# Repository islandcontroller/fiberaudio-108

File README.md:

# fiberaudio-108

A low-cost USB audio interface with S/PDIF optical output, based on the Cmedia CM108AH ASIC.

<p align="center"><picture>
  <source media="(prefers-color-scheme: dark)" srcset="doc/block-schem-wh.svg" />
  <source media="(prefers-color-scheme: light)" srcset="doc/block-schem.svg" />
  
</picture></p>

View [**Schematic**](doc/sch_fiberaudio-108_rev5.pdf) :page_facing_up: or [**PCB Preview**](https://htmlpreview.github.io/?https://github.com/islandcontroller/fiberaudio-108/blob/master/doc/ibom.html) :globe_with_meridians:. Customize using the [**CM108AH Configuration Tool**](sw/README.md) :cd:.

Production files will be made available on the [Releases](https://github.com/islandcontroller/fiberaudio-108/releases) page, once validation is complete.

### Key features

* Cmedia CM108AH audio interface ASIC
* 2.0 Stereo, up to 16-bit/48kHz (CD-DA equivalent)
* USB Mini-B input
* Optical S/PDIF output (JIS F05, e.g. TOSLINK&trade;)
* USB Audio Device Class 1.0, uses generic drivers
* Configuration EEPROM

## Overview

This USB audio interface provides a low-cost S/PDIF optical output for portable computers and tablet devices. Audio tranmission via optical link - as opposed to a wired line-level connection - eliminates hum caused by ground potential differences, and noise feed-through from switched-mode power supplies.

| Design Requirement | Solution Approach |
|--------------------|-------------------|
| Provide electrical isolation between device and audio equipment | Audio signal transmission via optical link (e.g. TOSLINK&trade;) |
| Compatibility for wide range of operating systems, with minimal driver maintenance | USB Audio Device Class using OS-provided generic drivers |
| IP accessibility for PCB design files | Use of free, open-source EDA tooling (e.g. KiCad) |
| Commonly-used, small form-factor USB connector, robust enough to withstand portable use | USB **mini**-B receptacle |
| Option for manual assembly | Passives no smaller than 0603. ICs leaded and no smaller than 0.5mm pin pitch (SSOP) |
| Low PCB production capability requirements | &bullet;&nbsp;FR4 base material<br/>&bullet;&nbsp;2-layer Cu, Top+Bot Mask, Top Overlay<br/>&bullet;&nbsp;&geq;0.25mm trace-to-outline<br/>&bullet;&nbsp;&geq;0.25mm trace width and spacing<br/>&bullet;&nbsp;&geq;0.35mm drill size<br/>&bullet;&nbsp;Gerber, NC Drill and RS274X outputs |

## Design Review (Prototyping)

Prototyping was carried out using **rev. 3** board design files, in a minimum-order batch of 5 PCBs, including automated assembly.

### Assembly

* Manual rework of the PCB around `U3` (SRV05-4) was required in order to fix the issues found in *rev. 3*, after production was already started.
* Parts `U1` (AT93C46D), `U2` (CM108AH), `SW1`, and both connectors were unavailable for automated assembly, and had to be retrofitted manually using hot-air reflow soldering.

### Software Support

* Drivers included with **SteamOS 3.0** provide full functionality out-of-box, including volume controls for S/PDIF output.

* Generic Audio Device drivers included in **Windows 7.1** (x64) as well as **Windows 10** (Version 22H2, x64) only support S/PDIF output in a passthrough mode. **Volume control and the mute input are inoperative when using the default driver package** (see below for workaround).

**Workaround:** ~~A vendor-specific Windows driver package for the CM108AH is available for download from the ASIC manufacturer's website: [https://www.cmedia.com.tw/support/download_center](https://www.cmedia.com.tw/support/download_center).~~

> Updated 08/2023: *Unfortunately, the ASIC manufacturer have stopped providing any drivers for download. I uploaded the latest signed driver package I could source (Version 8.1.8.2172) as [release `v0.1.5-driver-only`](https://github.com/islandcontroller/fiberaudio-108/releases/tag/v0.1.5-driver-only). Please check the file for integrity and verify it includes the correct signed driver binary before installing.*

~~Using the Windows device manager, perform a manual driver update of the `Generic USB PnP Sound Device`, and select `Win8\SoftwareDriver` from the extracted archive as the driver installation sources directory.~~

> Updated 08/2023: *To install the driver, extract the archive and right-click install the `Cm108.INF` file.*

After installation and a reboot, a new `Digital Audio (USB PnP Sound Device)` device will show up in the Sound Settings dialog, alongside the old `Speakers (USB PnP Sound Device)` device. 

**Disable** the `Speaker` device.

This workaround was tested using Windows 7.1 (x64), and Windows 10 (Version 22H2, x64).

### Device Configuration

* A configuration tool for re-programming the external EEPROM was developed and is provided in the [`sw/`](sw/) subdirectory.

* EEPROM access sporadically seems to return invalid data. Re-reading or re-programming the affected words can be used as a workaround.

### Summary

* The device works correctly in connection with Linux systems. For Windows hosts, a custom driver installation is required for the device to operate properly.

## Licensing

If not stated otherwise within the specific file, the contents of this project are licensed under the CERN Open Hardware Licence Version 2 - Permissive. The full license text is provided in the [`LICENSE`](LICENSE) document.

        SPDX-License-Identifier: CERN-OHL-P-2.0

This licensing model is compliant with the [Open Source Hardware Definition 1.0](https://www.oshwa.org/definition/).

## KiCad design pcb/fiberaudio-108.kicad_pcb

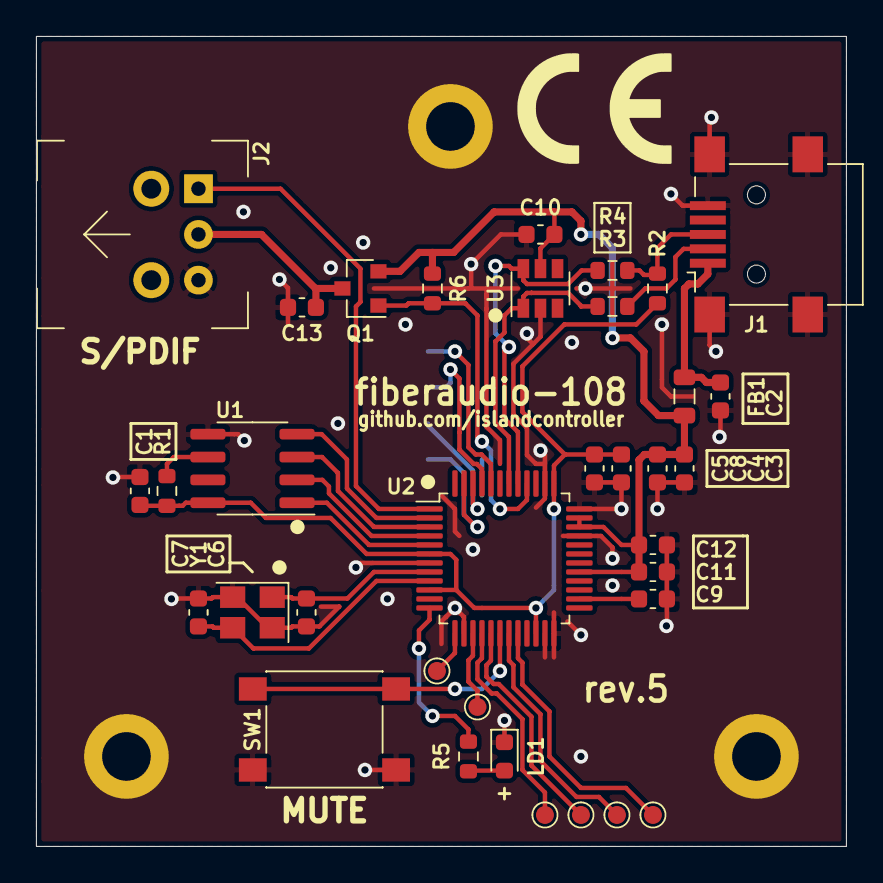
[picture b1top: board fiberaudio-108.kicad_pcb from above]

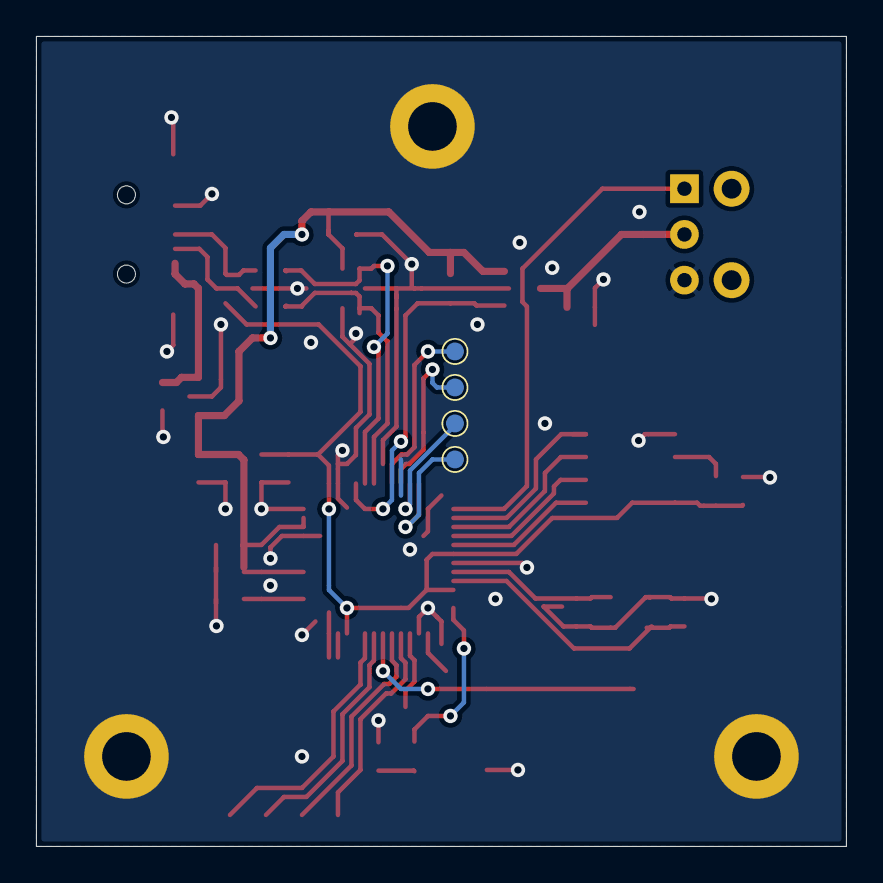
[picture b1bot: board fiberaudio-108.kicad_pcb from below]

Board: 2 copper layers, 45.0 x 45.0 mm, 42 parts (4 on the bottom side), 32 nets.

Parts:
C1, C3, C8, C10, C11, C12, C13: 100nF; C_0603_1608Metric
C2: 10nF; C_0603_1608Metric
C4, C5, C9: 4.7uF; C_0603_1608Metric
C6, C7: 20pF; C_0603_1608Metric
FB1: 100R@100MHz; L_0805_2012Metric
H1, H2, H3: MountingHole_Pad; MountingHole_2.7mm_M2.5_DIN965_Pad
J1: USB_B_Mini; USB_Mini-B_Lumberg_2486_01_Horizontal
J2: PLT133/T10W; PLT133_T10W
LD1: rd; LED_0603_1608Metric
Q1: SI2301CDS; SOT-23
R1: 0; R_0603_1608Metric
R2: 1k5; R_0603_1608Metric
R3, R4: 22; R_0603_1608Metric
R5: 330; R_0603_1608Metric
R6: 560; R_0603_1608Metric
SW1: MUTE; SW_SPST_PTS645
TP1: SDIN; TestPoint_Pad_D1.0mm
TP2: ADSCLK; TestPoint_Pad_D1.0mm
TP3: ADLRCK; TestPoint_Pad_D1.0mm
TP4: ADMCLK; TestPoint_Pad_D1.0mm
TP5: SDOUT; TestPoint_Pad_D1.0mm
TP6: DAMCLK; TestPoint_Pad_D1.0mm
TP7: DALRCK; TestPoint_Pad_D1.0mm
TP8: DASCLK; TestPoint_Pad_D1.0mm
TP9: GPIO3; TestPoint_Pad_D1.0mm
TP10: GPIO4; TestPoint_Pad_D1.0mm
U1: AT93C46D; SOIC-8_3.9x4.9mm_P1.27mm
U2: CM108AH; LQFP-48_7x7mm_P0.5mm
U3: SRV05-4; SOT-23-6
Y1: 12MHz; Crystal_SMD_3225-4Pin_3.2x2.5mm

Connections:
+3V3: C1.1, C5.1, C8.1, R1.1, R2.1, U1.8, U2.6, U2.10, U2.22, U2.37
+5V: C3.1, C4.1, C10.1, C11.1, C12.1, FB1.1, Q1.2, R6.1, U2.29, U2.34, U2.35, U3.5
/EECS: U1.1, U2.5
/EEMISO: U1.4, U2.2
/EEMOSI: U1.3, U2.3
/EESK: U1.2, U2.4
/LEDO: R5.2, U2.12
/MUTE: SW1.2, U2.18
/SPDIF_MOD: J2.1, U2.1
/SPDIF_PWDN: Q1.1, R6.2, U2.40
/USBD_IN_N: J1.2, R3.2
/USBD_IN_P: J1.3, R2.2, R4.2
/USBD_N: R3.1, U2.42, U3.1
/USBD_P: R4.1, U2.41, U3.6
/VBUS: C2.1, FB1.2, J1.1
GND: C1.2, C2.2, C3.2, C4.2, C5.2, C6.2, C7.2, C8.2, C9.2, C10.2, C11.2, C12.2, C13.2, H1.1, H2.1, H3.1, J1.5, J1.6, J2.3, LD1.1, SW1.1, U1.5, U2.7, U2.14, U2.23, U2.24, U2.33, U2.36, U2.38, U3.2, Y1.2, Y1.4
unnamed: C6.1, U2.8, Y1.1
unnamed: C7.1, U2.9, Y1.3
unnamed: C9.1, U2.26
unnamed: C13.1, J2.2, Q1.3
unnamed: LD1.2, R5.1
unnamed: R1.2, U1.6
unnamed: TP1.1, U2.16
unnamed: TP2.1, U2.17
unnamed: TP3.1, U2.19
unnamed: TP4.1, U2.20
unnamed: TP5.1, U2.44
unnamed: TP6.1, U2.45
unnamed: TP7.1, U2.46
unnamed: TP8.1, U2.47
unnamed: TP9.1, U2.13
unnamed: TP10.1, U2.15

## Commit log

2021-01-08 Fix block diagram centering
2021-01-08 Add description, design requirements
2021-01-08 Add license
2021-01-09 Fix block diagram background fills
2021-01-09 Add initial PCB files
2021-01-09 Add schematic, custom components and initial layout
2021-01-09 Add schematic print
2021-01-09 Fix typo in schematic
2021-01-09 Add initial routed layout
2021-01-10 Redesign for automated assembly
2021-01-10 Added testpoints; Removed erroneous file
2021-01-10 Updated schematic to rev3
2021-01-10 Adjust thermal relief to help prevent tombstoning
2021-01-11 Adjust PCB page layout for print
2021-01-11 Update project status to prototyping
2021-01-12 Fix USBD disco at U3; Adjust VBUS/+5 routing; Update to rev.4
2021-01-15 Fix USB connector type in README; Add information about audio data rate
2021-01-22 Replace clamp diode array DS; Add XTAL datasheet
2021-01-26 Add design review results for prototyping run
2021-01-29 Add EEPROM access information
2021-02-04 Add configuration tool
2021-02-04 Update design review results for EEPROM access
2021-02-06 Fix list type hints for Python 3.8
2021-02-08 Update EEPROM access availability notes
2021-02-25 Add PMOS datasheet
2021-02-25 Add alternative P/Ns, RES tolerance values
2021-02-25 Rev. 5; Add ALTN part for ESD diode; Adjust layout
2021-02-26 Add GPIO control support to config tool
2021-02-26 Add button state readout to config tool
2021-02-26 Add PCB preview
2022-05-14 Add review notes for SteamOS support
2023-08-25 Add driver package notice; Update latest tested Windows OS version
2023-08-25 Add dark-mode block schematic
2023-10-09 Resolve #1: Expand device search to cover all Cmedia devices by default; Add cmdline fields for custom VID and PID
2023-10-09 Add highlighted link to configuration tool; Replace PDF icon
2023-10-09 Add note regarding possibly unsupported devices in listing
2024-11-08 Fix incorrect manufacturer and product name length limits
2024-11-08 Remove read-back verification and re-tries for EEPROM write access
2025-12-17 Mods for CM108B
    Added adc,dac,aa valid flags to configuration and modified code to read them and write to eeprom
    Added an "explainer" of eeprom data to be written more verbosely
2025-12-17 Bug solve + read + verify
    Solved bug where data[42] was left in code, it shouldn't be there
    Read8 modified with time.sleep, verify on write works properly now
2026-02-21 Add automatic white-space trimming; Fix cm108ah.py formatting
2026-02-21 Add garbage check and automatic retry for read function
